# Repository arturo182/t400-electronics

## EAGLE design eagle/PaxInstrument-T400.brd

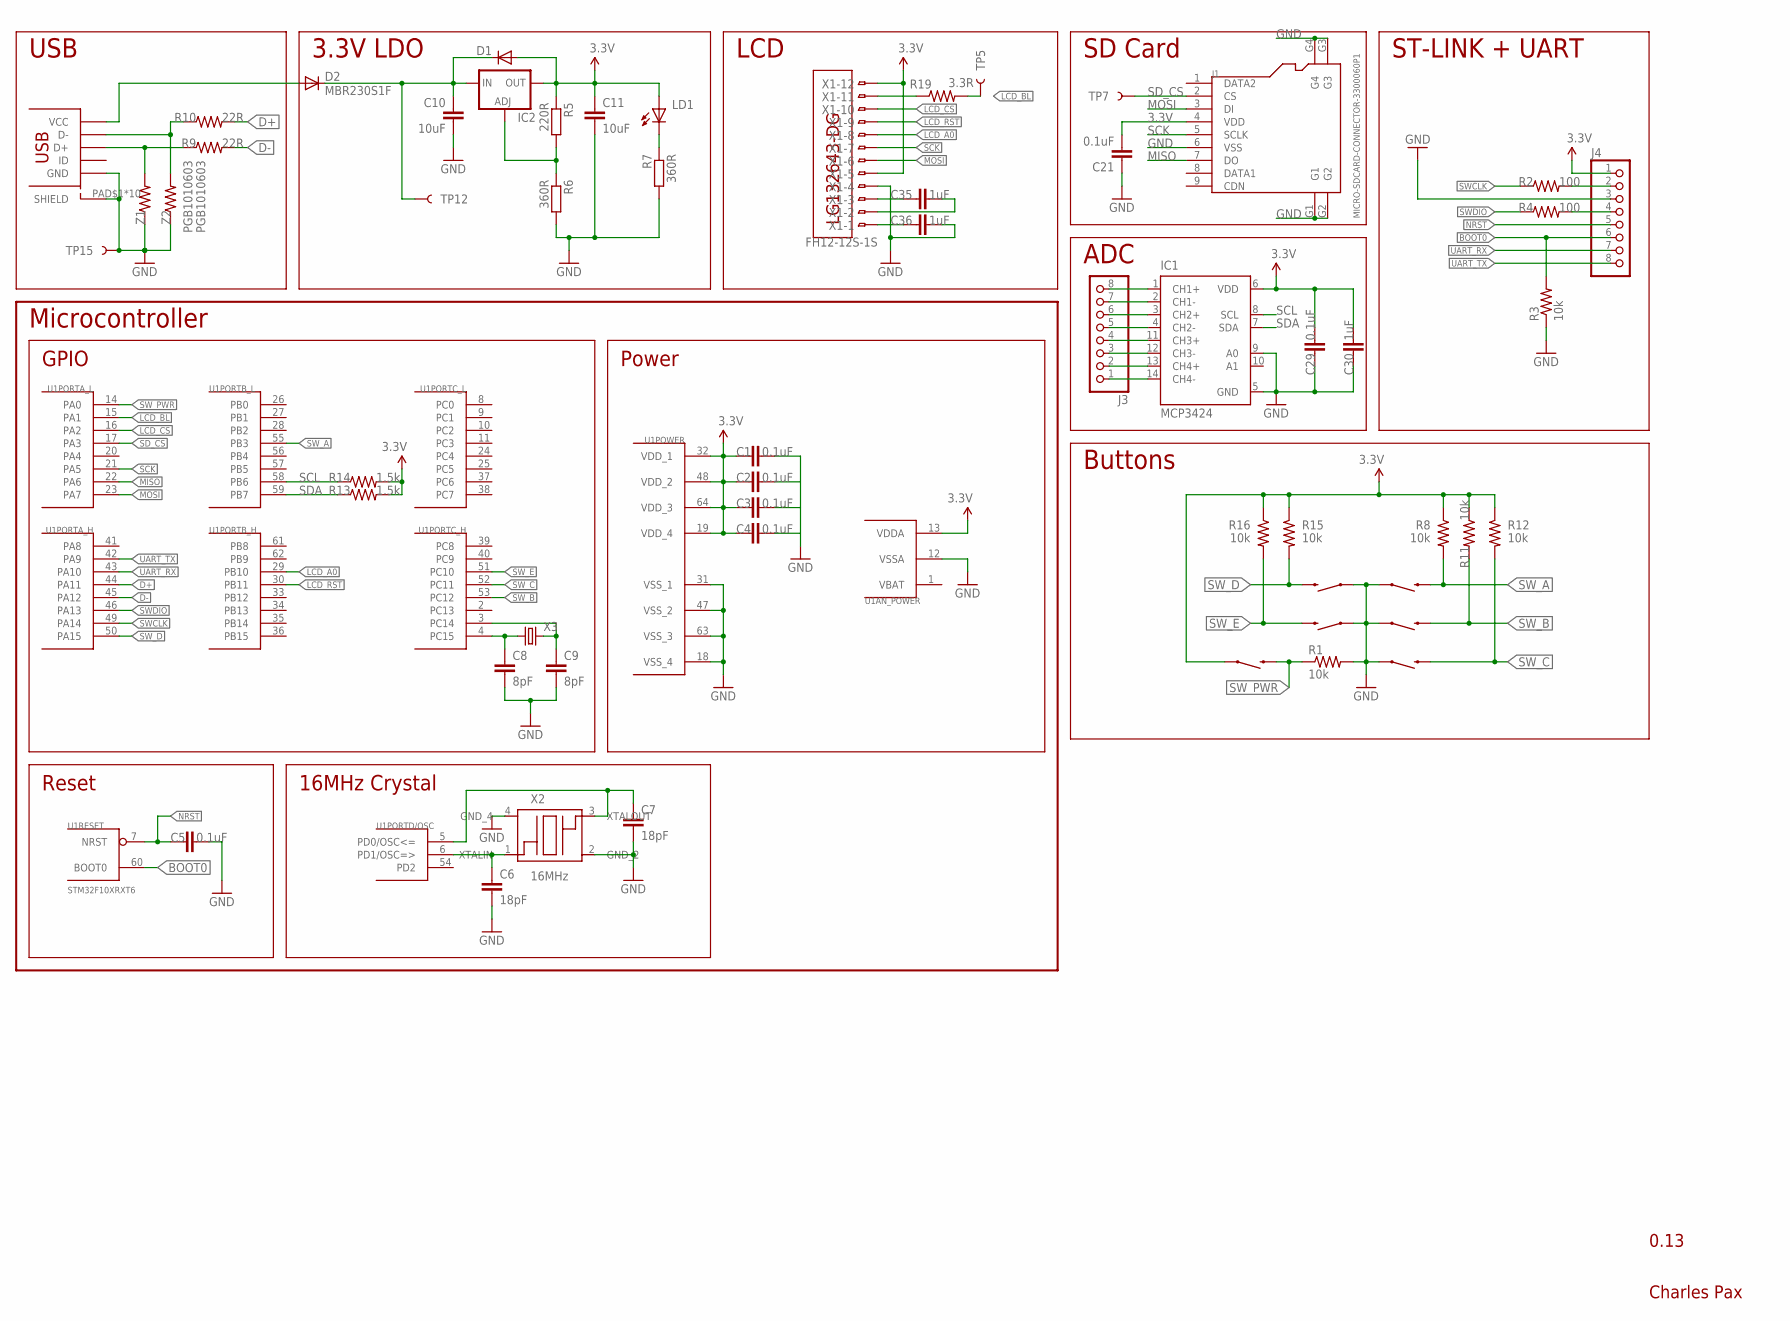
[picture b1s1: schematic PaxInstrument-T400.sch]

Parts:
C1, C2, C3, C4, C5, C21, C29: 0.1uF; SPARKFUN-CAPACITORS_0603-CAP
C6, C7: 18pF; SPARKFUN-CAPACITORS_0603-CAP
C8, C9: 8pF; SPARKFUN-CAPACITORS_0603-CAP
C10, C11: 10uF; 0603
C30, C35, C36: 1uF; SPARKFUN-CAPACITORS_0603-CAP
D1: 1N4148W; SOD-123_MINI-SMA
D2: MBR230S1F; SOD123; MPN MBR230S1F-7
IC1: MCP3424; SO14; MPN MCP3424-E/SL
IC2: LM317AEMP; SOT223
J1: MICRO-SDCARD-CONNECTOR-3300060P1; 9P-SMD-W-RING; MPN ST-TF-003A
J2: USB_MICROSMT+THRUHULE; USB_MICRO_THRUHOLE; MPN 10118194-0001LF
J3, J4: PINHD-1X8; 1X08
LD1: LEDCHIPLED_0805; CHIPLED_0805
R1, R3, R8, R11, R12, R15, R16: 10k; SPARKFUN-RESISTORS_0603-RES
R2, R4: 100; SPARKFUN-RESISTORS_0603-RES
R5: 220R; 0603
R6, R7: 360R; 0603
R9, R10: 22R; SPARKFUN-RESISTORS_0603-RES
R13, R14: 1.5k; SPARKFUN-RESISTORS_0603-RES
R19: 3.3R; SPARKFUN-RESISTORS_0603-RES
S1, S2, S3, S4, S5, S6: SWITCH-MOMENTARY-2SMD; TACTILE_SWITCH_SMD; MPN RS-187R05A2-DS MT RT
TP5: LCD_BL; TP_15TH; MPN N/A
TP7: SD_CS; TP_15TH; MPN N/A
TP12: VBUS; TP_15TH; MPN N/A
TP15: GND; TP_15TH; MPN N/A
U1: STM32F10XRXT6; TQFP64
U$5: LG132643-DG; MPN LG132643-DW
X1: FH12-12S-1S; FH12-12S-1SH; MPN FH12-12S-1SH(55)
X2: 16MHz; FA-238
X3: CRYSTALTC26H; TC26H
Z1, Z2: PGB1010603; SPARKFUN-RESISTORS_0603-RES; MPN PGB1010603NRHF

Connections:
3.3V: C1.1, C2.1, C3.1, C4.1, C11.1, C21.2, C29.1, C30.1, D1.A, IC1.6 (VDD), IC2.2 (OUT), IC2.4 (OUT), J1.4 (VDD), J4.1, LD1.A, R5.1, R8.1, R11.1, R12.1, R13.2, R14.2, R15.1, R16.1, S6.1, U1.13 (VDDA), U1.19 (VDD_4), U1.32 (VDD_1), U1.48 (VDD_2), U1.64 (VDD_3), X1.5, X1.12
ADC_CH1_N: IC1.2 (CH1-), J3.7
ADC_CH1_P: IC1.1 (CH1+), J3.8
ADC_CH2_N: IC1.4 (CH2-), J3.5
ADC_CH2_P: IC1.3 (CH2+), J3.6
ADC_CH3_N: IC1.12 (CH3-), J3.3
ADC_CH3_P: IC1.11 (CH3+), J3.4
ADC_CH4_N: IC1.14 (CH4-), J3.1
ADC_CH4_P: IC1.13 (CH4+), J3.2
BOOT0: J4.6, R3.2, U1.60 (BOOT0)
D+: R10.2, U1.44 (PA11)
D-: R9.2, U1.45 (PA12)
GND: C1.2, C5.2, C6.2, C7.2, C8.2, C9.2, C10.2, C11.2, C21.1, C29.2, C30.2, C36.1, IC1.5 (GND), IC1.9 (A0), J1.6 (VSS), J1.G1, J1.G2, J1.G3, J1.G4, J2.PAD$1 (SHIELD), J2.PAD$2 (SHIELD), J2.PAD$3 (SHIELD), J2.PAD$4 (SHIELD), J2.PAD$5 (SHIELD), J2.PAD$6 (SHIELD), J2.PAD$7 (SHIELD), J2.PAD$8 (SHIELD), J2.PAD$9 (SHIELD), J2.PAD$10 (SHIELD), J2.PIN$5 (GND), J4.3, R1.2, R3.1, R6.2, R7.2, S1.1, S2.1, S3.1, S4.1, S5.1, TP15.P$1, U1.12 (VSSA), U1.18 (VSS_4), U1.31 (VSS_1), U1.47 (VSS_2), U1.63 (VSS_3), X1.4, X2.2 (GND_2), X2.4 (GND_4), Z1.1, Z2.1
LCD_A0: U1.29 (PB10), X1.8
LCD_BL: R19.2, TP5.P$1, U1.15 (PA1)
LCD_CS: U1.16 (PA2), X1.10
LCD_RST: U1.30 (PB11), X1.9
MISO: J1.7 (DO), U1.22 (PA6)
MOSI: J1.3 (DI), U1.23 (PA7), X1.6
unnamed: C7.1, U1.5 (PD0/OSC<=), X2.3 (XTALOUT)
unnamed: R19.1, X1.11
unnamed: C6.1, U1.6 (PD1/OSC=>), X2.1 (XTALIN)
unnamed: IC2.1 (ADJ), R5.2, R6.1
unnamed: LD1.C, R7.1
unnamed: C8.1, U1.4 (PC15), X3.1
unnamed: C9.1, U1.3 (PC14), X3.2
unnamed: J4.2, R2.2
unnamed: J4.4, R4.2
unnamed: J2.PIN$2 (D-), R10.1, Z2.2
unnamed: J2.PIN$3 (D+), R9.1, Z1.2
unnamed: C35.1, X1.3
unnamed: C35.2, X1.2
unnamed: C36.2, X1.1
NRST: C5.1, J4.5, U1.7 (NRST)
SCK: J1.5 (SCLK), U1.21 (PA5), X1.7
SCL: IC1.8 (SCL), R14.1, U1.58 (PB6)
SDA: IC1.7 (SDA), R13.1, U1.59 (PB7)
SD_CS: J1.2 (CS), TP7.P$1, U1.17 (PA3)
SWCLK: R2.1, U1.49 (PA14)
SWDIO: R4.1, U1.46 (PA13)
SW_A: R8.2, S3.3 (2), U1.55 (PB3)
SW_B: R11.2, S2.3 (2), U1.53 (PC12)
SW_C: R12.2, S1.3 (2), U1.52 (PC11)
SW_D: R15.2, S4.3 (2), U1.50 (PA15)
SW_E: R16.2, S5.3 (2), U1.51 (PC10)
SW_PWR: R1.1, S6.3 (2), U1.14 (PA0)
UART_RX: J4.7, U1.43 (PA10)
UART_TX: J4.8, U1.42 (PA9)
VBAT: U1.1 (VBAT)
VBUS: C10.1, D1.C, D2.C, IC2.3 (IN), TP12.P$1
VBUS_IN: D2.A, J2.PIN$1 (VCC)

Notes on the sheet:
ADC
USB
LCD
Buttons
Microcontroller
0.13
Charles Pax
SD Card
3.3V LDO
ST-LINK + UART
GPIO
Power
Reset
16MHz Crystal

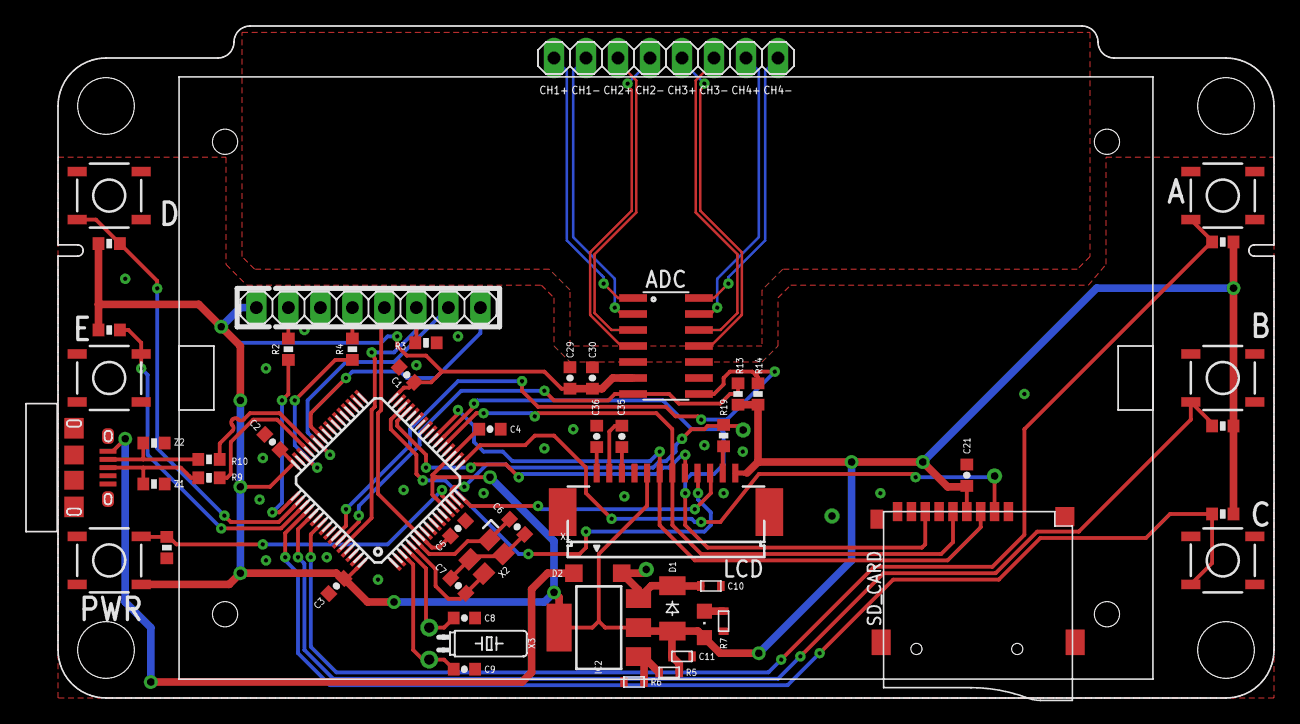
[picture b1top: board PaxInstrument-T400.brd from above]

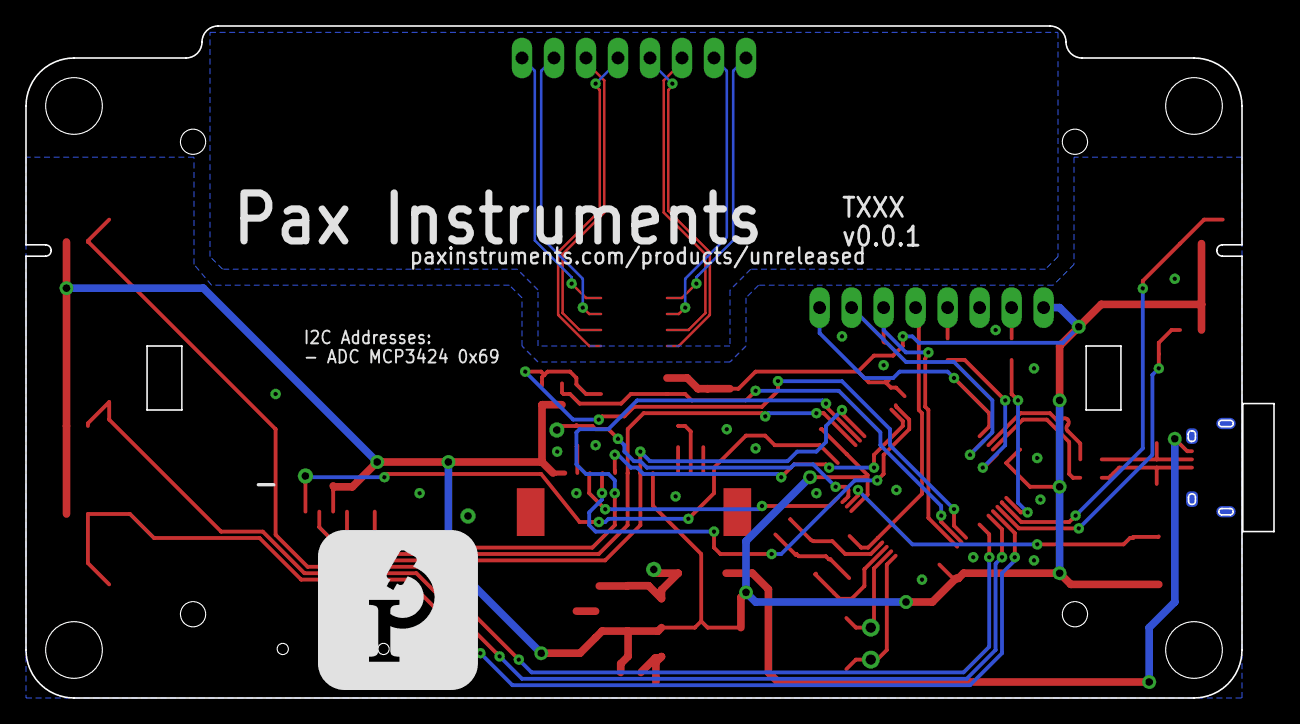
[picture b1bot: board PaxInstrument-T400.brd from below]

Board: 2 copper layers, 99.1 x 53.3 mm, 60 parts (2 on the bottom side), 50 nets.

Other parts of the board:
U$6: PAX-LOGO-0.5IN

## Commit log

2016-05-12 Remove a lot and replace atmega with stm32f103
2016-05-12 Moved a trace that was inside the LCD cutout

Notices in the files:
parts and their libraries:
SparkFun-Electromechanical: Licensing: CC v3.0 Share-Alike You are welcome to use this library for commercial purposes.
